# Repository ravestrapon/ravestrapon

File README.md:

# ravestrapon
Source repository for ravestrapon source material and board design

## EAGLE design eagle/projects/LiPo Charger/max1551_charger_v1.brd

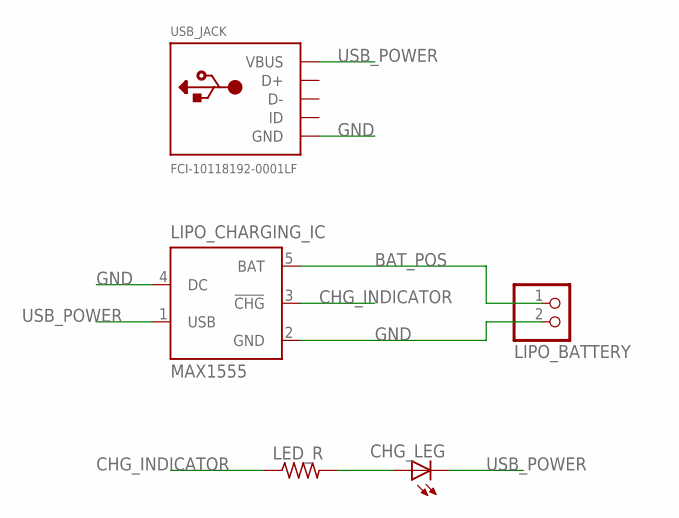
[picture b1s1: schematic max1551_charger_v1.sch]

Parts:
CHG_LEG: LED3MM
LED_R: R-US_0207/2V; 0207/2V
LIPO_BATTERY: JST_2PIN-SMT-RA; JST-PH-2-SMT-RA
LIPO_CHARGING_IC: MAX1555; SOT23-5L
USB_JACK: FCI-10118192-0001LF

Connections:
BAT_POS: LIPO_BATTERY.1 (2), LIPO_CHARGING_IC.5 (BAT)
CHG_INDICATOR: LED_R.1, LIPO_CHARGING_IC.3 (!CHG)
GND: LIPO_BATTERY.2 (1), LIPO_CHARGING_IC.2 (GND), LIPO_CHARGING_IC.4 (DC), USB_JACK.GND
unnamed: CHG_LEG.A, LED_R.2
USB_POWER: CHG_LEG.K (C), LIPO_CHARGING_IC.1 (USB), USB_JACK.VCC (VBUS)

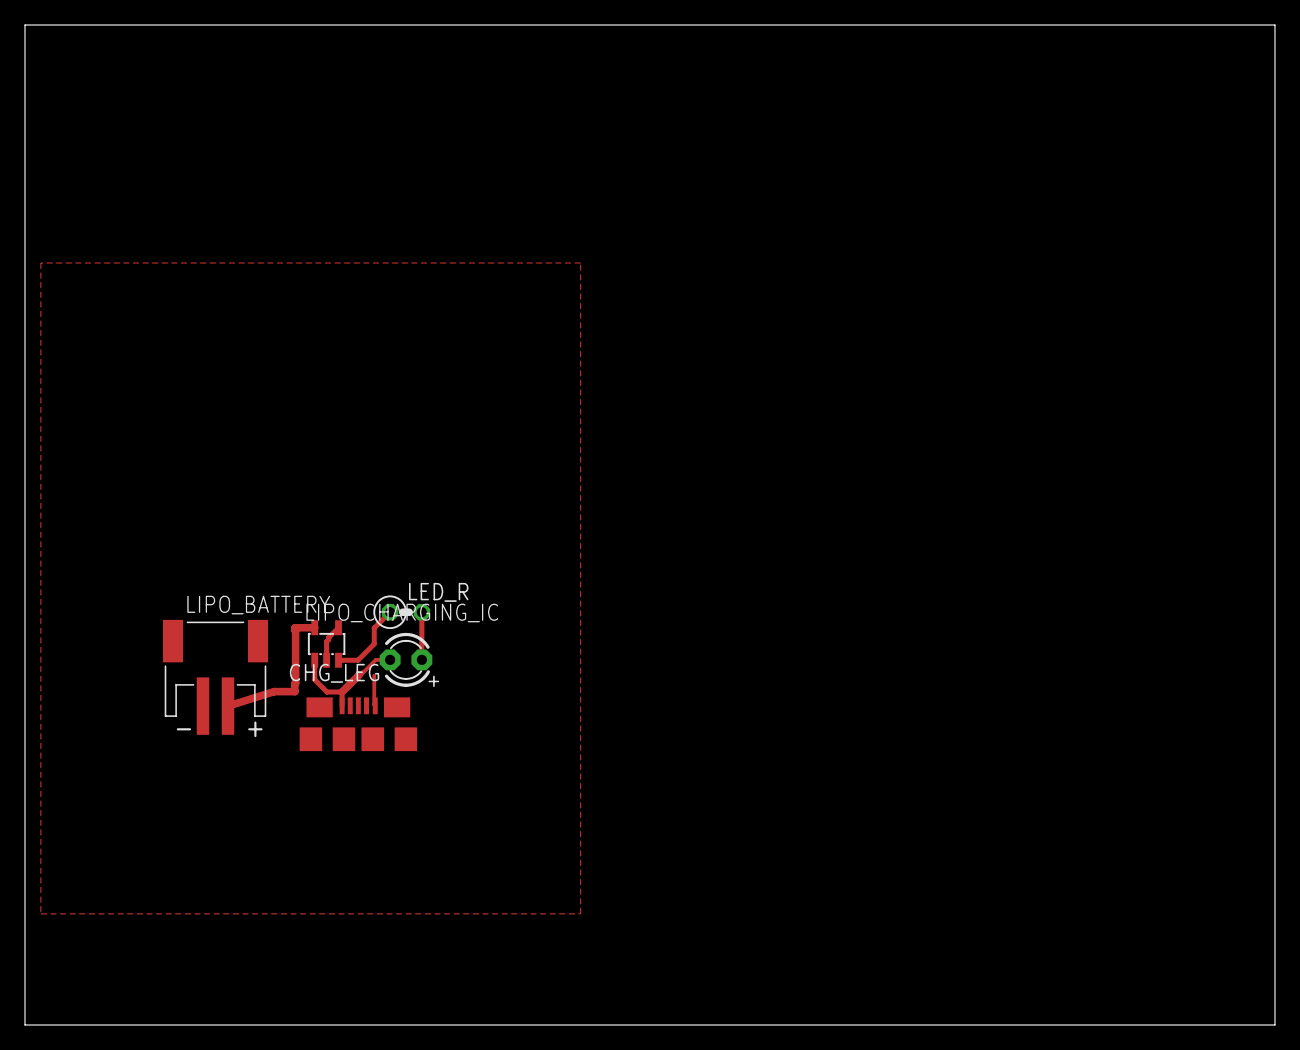
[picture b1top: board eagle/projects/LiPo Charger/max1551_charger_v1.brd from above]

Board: 2 copper layers, 100.0 x 80.0 mm, 5 parts (0 on the bottom side), 5 nets.

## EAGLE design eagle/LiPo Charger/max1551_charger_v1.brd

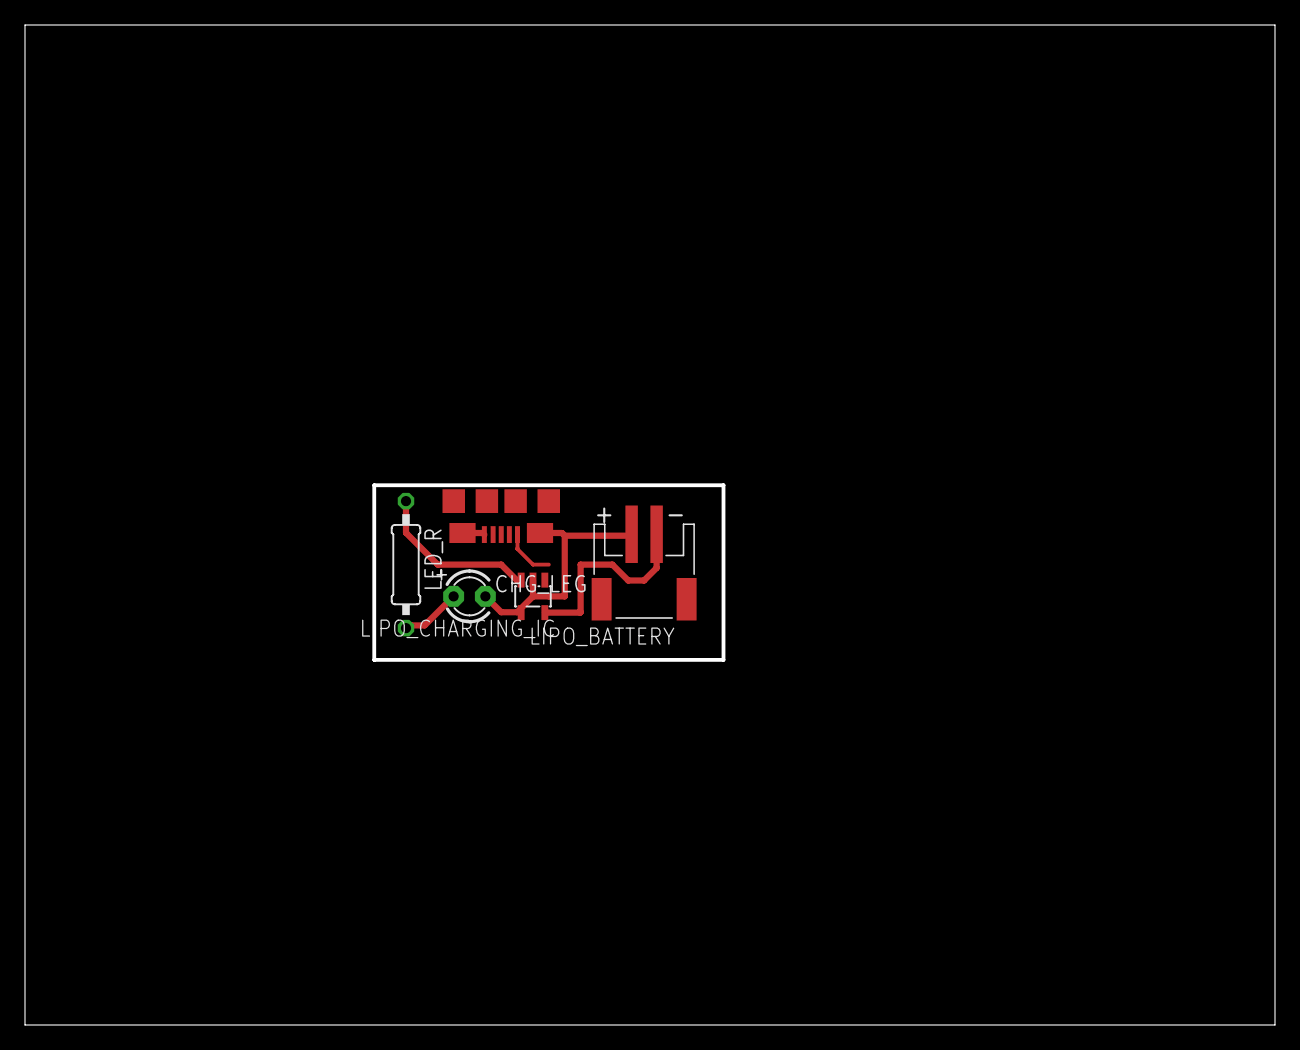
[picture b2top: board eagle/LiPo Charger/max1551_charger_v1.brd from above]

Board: 2 copper layers, 100.0 x 80.0 mm, 5 parts (0 on the bottom side), 5 nets.

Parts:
CHG_LEG: LED3MM
LED_R: 0207/10
LIPO_BATTERY: JST-PH-2-SMT-RA
LIPO_CHARGING_IC: MAX1555; SOT23-5L
USB_JACK: FCI-10118192-0001LF

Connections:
BAT_POS: LIPO_BATTERY.2, LIPO_CHARGING_IC.5
CHG_INDICATOR: LED_R.1, LIPO_CHARGING_IC.3
unnamed: CHG_LEG.A, LED_R.2
unnamed: CHG_LEG.K, LIPO_BATTERY.1, LIPO_CHARGING_IC.2, LIPO_CHARGING_IC.4, USB_JACK.GND@1, USB_JACK.GND@2, USB_JACK.GND@3, USB_JACK.GND@4, USB_JACK.GND@5, USB_JACK.GND@6, USB_JACK.GND@7
USB_POWER: LIPO_CHARGING_IC.1, USB_JACK.VCC

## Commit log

2017-11-27 Lipo Charging Test Board
    This includes the EagleCAD source for a LiPo Charging test board.
2017-11-27 Fixing the LiPo Part # from 1555 to 1551
2017-11-27 Adding the lost files, oops
2017-11-27 Add the website data
    This adds in the website data and the upload script.
    The script requires ssh keys to communicate with the server,
    but otherwise all the data is here.
2017-11-27 Add Mac support to website updater script
    It looks like the ~ in the website updater script doesn't work
    nicely on mac. Replacing it with ${HOME} seems to function just
    fine though.
2017-11-27 Add github & instagram links to website
2017-11-27 Remove uneeded argument
    There was an unnessicary exception added to the rsync command since
    we're not storing the ssh keys in with src anymore (now that the code is
    on github)
2017-11-27 Move eagle projects to better match Eagle structure
    This moves the Eagle projects into their own folder called
    projects/ that can be added to the "directories" strings in Eagle
    more easily (instead of having to set up symlinks/etc)
2017-11-30 Update LiPo Charger with MAX 1551
    This board was printed and tested and it seems to work.
    It's a bit simple/slow though so a better charger circuit
    would probably be advantageous in the future. Plus the
    MAX1551 charger ICs are expensive ~$2 each.
    However, it works! So I'm saving these designs for later
2017-12-28 Adding battery monitor sketch
    This is a simple sketch I'm using to monitor the
    voltage of a test battery over time. Essentially this
    sketch just reads off ADC0 at regular intervals and
    converts that into a voltage reading. That value
    is then printed onto the serial port, which can
    be logged by a host computer to get a graph of voltage
2017-12-28 Adding support for a second voltage to monitor
    This adds in support for a voltage to monitor on
    A1 as well, this input is assumed to have a 1/2 voltage
    divider attached to it (to allow it to measure larger
    voltages)
2017-12-28 Fix buffering issues with perl
    There was a buffering issue that prevented you
    from using "tee" on the collect_logs.sh script which
    is obviously what you'd want to to with such a script.
    This patch forces perl to flush stdout and now tee, grep,
    and other such programs should work on the output
2017-12-28 Use internal ADC reference for battery monitor
    Using the internal 2.56V reference voltage instead
    of Vcc for measuring the battery voltages. This makes it
    much more accurate, but requires the use of external
    voltage dividers to bring the signals into range, so the
    SW has to compensate. This patch also includes precisely
    computed scalers for each of the probes on my battery
2017-12-28 Speed up sampling and change pin #
2017-12-28 Add Script to plot battery monitor output
    This uses matplotlib to make a more human-readable
    chart of the power testing graphs
2017-12-28 Add an auto-updating server for showing battery monitor plots
2017-12-28 Add ATMega16 testing code
    This is a simple Hello World program to blink an
    LED and set up the fuses on an ATMega16. This proves
    that the programmer and the circuit board are all working :D
2017-12-28 Clear the plots
    Before this after repeated reloads would fill memory up. Now
    the plot image is cleared after each reload
2017-12-28 Adding in the first draft of the actual src
    This is heavily copied from another project of mine
    but most importantly includes a build.sh that can compile
    and flash using my ATmega16 board. This is tricky because
    FastLED needs Arduino, and I'm not using Arduino to update
    nor is there an ATmega16 Arduino. So this requires:
    MightyCore installed in your Arduino install. This adds ATmega16
2017-12-28 Add connection test to build script
    This adds a simple connection test to the build script so it
    can give more informative errors. Without this, when you don't
    have the programmer or mcu plugged in, the error messages are
    about fuses which can be confusing. This way it fails earlier
    and it's clear you just need to check your connections and the
    error has nothing to do with setting fuses.
2017-12-29 Purge outdated references to pole/ball in animations
    The original project I wrote these animations for was a vertical
    art installation with a large ball on top of a pole. As such these
    animations had to control these two kinds of lights, but is now
    overkill since the new design has only a "pole" (so-to-speak).
    This CL just cleans up the animation code and gets rid of these
    confusing references.
2017-12-29 Add Instagram feed to the website
    This adds a little widget to the website that pulls down the
    pictures of instagram daily. It's free so it doesn't update
    more than 1/day but that's just fine for our purposes!
2017-12-29 Remove erroneous 1s pause
    For some reason there was a 1s pause after each pass
    through the animations. This caused a weird glitch
    each time it restarted at the top of the list again.
    This patch just removes this delay. It looks much smoother
    without it and I think it was just a forgotten leftover
    piece of a test or something.
2018-01-02 Add support for buttons & Fuel gauge
    This is rudamentary support for a "fuel gauge" on ADC4, which
    is meant to be wired to a 1/2 voltage divider connected to the
    battery voltage.
    The two buttons are wired to external interrupts 0 & 1 so they
    can be interrupt-driven buttons, which is also new. The code is
    somewhat janky for this and can't interrupt the animations yet
2018-01-05 Minor changes while testing
2018-01-18 Add in example of how to detect if USB is connected
    This is temporary code not meant to be left in forever, but
    rather it'll just function as a reminder of how to do it in the
    future.
2018-01-18 Refactor for interruptable animations
    Previously there was no good was to interrupt an animation due
    to the way they were implimented. This new OOP method should
    fascilitate a more regular frame rate and allow you to interrupt
    them which is required for a fuel gauge to work right.
    Only a couple animations are refactored now. More to follow
2018-01-18 Porting Static Animation to new OOP model
2018-01-18 Adding in forgotten fuel guage testing code
2018-01-18 Ported Blockify Animation to new style
2018-01-18 Port over the Pulse animation to the new style
2018-01-18 Porting Rainbow animation to the new style
2018-01-18 Porting Tracer animation over to the new style
2018-01-18 Port over Drop animation to new style (all done)
2018-01-18 Fixing a few minor bugs in the Drop animation
2018-01-18 Fix memory leak -- delete old Animation objects
    This was a silly mistake, we should definitely be deleting old
    Animation objects once we're done with them!
2018-01-19 Adding a frame count to animations
    This allows the animation to be totally selfcontained -- now
    the nextFrame() function returns a bool (indicating if it's
    generated as many frames as expect already) and the main loop
    can just move on when it says false. This means we can just push
    a whole new animation into place and it'll restart right back
    where it expected. This will allow interrupting animations (like
2018-01-19 Adding in the accidentally omitted rainbow animation
2018-01-19 Realign superclass constructor call
2018-01-19 Add an interrupting Fuel Guage
    The fuel guage now "works" although the animation is lame right now.
    When you press the button a Fuel Guage animation is pushed into place
    over whatever the current animation is and then run out before it
    returns to that same animation seamlessly. No more waiting for an
    animation to complete before the battery status is revealed! Next, I
    need to make it look better, check if power is plugged in, and possibly
2018-01-19 Keep the fuel guage on as long as the btn is down
    This is a slick user interface upgrade. As long as the user
    holds down the button the battery level will keep being displayed.
    If you don't hold it down though, it'll just play for a little bit
    and then stop, do you don't *have* to hold it down if you don't
    want to. Also this adds a pulsing animation to the fuel guage that
    greatly upgrades it's appearance
2018-01-19 Formalize how interrupting animations work
    This makes it clear that there is only 1 "standby" animation and
    it is a slot reserved for the "normal" animation that was first
    interrupted. Repeated interruptions will erase the existing interrupting
    animation from memory. This prevents the stack from building up
    and give a more responsive feel.
2018-01-20 Style cleanup
2018-01-20 Fixing the interrupt #s in comments
2018-01-20 Moving the brightness change work out of the ISR
    In an effort to standardize my system and remove as much work as
    possible from the ISR, this patch changes the actual work for
    changing brightnessed into the main loop. Similar to how other
    interruptions should/are handled.
2018-01-20 Add in USB power detection to the fuel gauge.
    This CL adds in the logic to the fuel gauge to make sure that the USB
    power cable isn't plugged in when it's doing it's readings. If it is,
    then it plays the "currently charging" animation instead of the "fuel
    gauge" one, to let the user know that it's plugged in. The animation
    isn't the greatest right now, but the plumbing is all in place.
    Still to do:
2018-01-20 Better "currently charging" animation
2018-01-23 Make the system more robust to errors
    This is accomplished by enabling a watchdog timer. The WDT reboots
    the microcontroller if it doesn't get reset for 60ms. This shouldn't
    happen unless something is awry though -- because the WDT gets reset
    right before attempting to generate a new frame. There should definitely
    be a new frame generated at least once every 60ms, so if that isn't
    happening it makes sense to reboot the whole microcontroller.
